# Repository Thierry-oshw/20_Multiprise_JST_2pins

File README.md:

# 20_Multiprise_JST_2pins
 Simple plaquette permettant de faire des multiprises

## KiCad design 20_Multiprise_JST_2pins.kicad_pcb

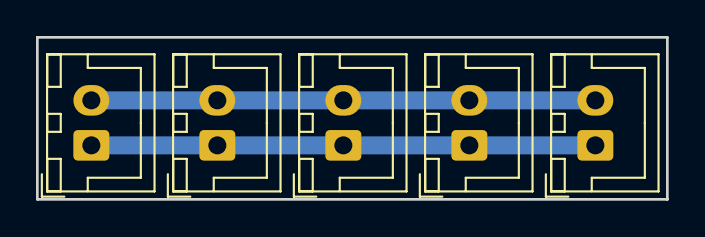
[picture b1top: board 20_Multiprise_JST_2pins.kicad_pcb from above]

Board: 2 copper layers, 35.0 x 9.0 mm, 5 parts (0 on the bottom side), 2 nets.

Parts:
J1, J2, J3, J4, J5: Conn_01x02; JST_XH_B2B-XH-A_1x02_P2.50mm_Vertical

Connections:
pin1: J1.1, J2.1, J3.1, J4.1, J5.1
pin2: J1.2, J2.2, J3.2, J4.2, J5.2

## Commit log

2021-06-09 schema + routage
2021-06-10 ajout licence cern
2021-07-26 maj split librairies
2023-05-02 chgt nom fichier licence
